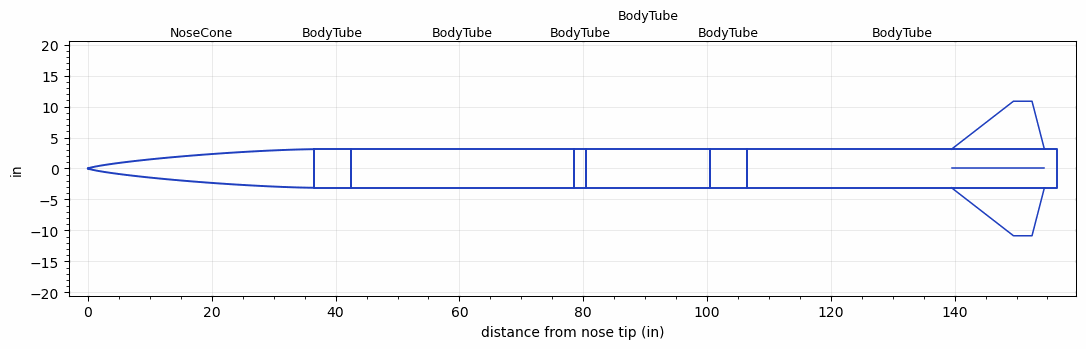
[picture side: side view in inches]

<RASAeroDocument>
 <FileVersion>2</FileVersion>
 <RocketDesign>
  <NoseCone>
   <Length>36.5</Length>
   <Diameter>6.23</Diameter>
   <Shape>Von Karman Ogive</Shape>
   <BluntRadius>0.05</BluntRadius>
   <Location>0</Location>
  </NoseCone>
  <BodyTube>
   <Length>6</Length>
   <Diameter>6.23</Diameter>
   <Location>36.5</Location>
  </BodyTube>
  <BodyTube>
   <Length>36</Length>
   <Diameter>6.23</Diameter>
   <Location>42.5</Location>
  </BodyTube>
  <BodyTube>
   <Length>2</Length>
   <Diameter>6.23</Diameter>
   <Location>78.5</Location>
   <Protuberance>
    <StreamlinedNoBaseDrag>0</StreamlinedNoBaseDrag>
    <StreamlinedWithBaseDrag>0.122</StreamlinedWithBaseDrag>
    <InclinedPlate1Angle>0</InclinedPlate1Angle>
    <InclinedPlate1FrontalArea>0</InclinedPlate1FrontalArea>
    <InclinedPlate2Angle>0</InclinedPlate2Angle>
    <InclinedPlate2FrontalArea>0</InclinedPlate2FrontalArea>
   </Protuberance>
  </BodyTube>
  <BodyTube>
   <Length>20</Length>
   <Diameter>6.23</Diameter>
   <Location>80.5</Location>
  </BodyTube>
  <BodyTube>
   <Length>6</Length>
   <Diameter>6.23</Diameter>
   <Location>100.5</Location>
   <Protuberance>
    <StreamlinedNoBaseDrag>1.87</StreamlinedNoBaseDrag>
    <StreamlinedWithBaseDrag>0</StreamlinedWithBaseDrag>
    <InclinedPlate1Angle>0</InclinedPlate1Angle>
    <InclinedPlate1FrontalArea>0</InclinedPlate1FrontalArea>
    <InclinedPlate2Angle>0</InclinedPlate2Angle>
    <InclinedPlate2FrontalArea>0</InclinedPlate2FrontalArea>
   </Protuberance>
  </BodyTube>
  <BodyTube>
   <Length>50</Length>
   <Diameter>6.23</Diameter>
   <LaunchShoeArea>0.183</LaunchShoeArea>
   <Location>106.5</Location>
   <Fin>
    <Count>4</Count>
    <Chord>15</Chord>
    <Span>7.75</Span>
    <SweepDistance>10</SweepDistance>
    <TipChord>3</TipChord>
    <Thickness>0.255</Thickness>
    <LERadius>0.0313</LERadius>
    <Location>17</Location>
    <AirfoilSection>Hexagonal</AirfoilSection>
    <FX1>0.35</FX1>
    <FX3>0.35</FX3>
   </Fin>
  </BodyTube>
  <Surface>Smooth Paint</Surface>
  <ModifiedBarrowman>True</ModifiedBarrowman>
  <Turbulence>True</Turbulence>
  <UseBooster1>False</UseBooster1>
  <UseBooster2>False</UseBooster2>
 </RocketDesign>
 <LaunchSite>
  <Altitude>2930</Altitude>
  <Pressure>0</Pressure>
  <RodAngle>5</RodAngle>
  <RodLength>17</RodLength>
  <Temperature>85</Temperature>
  <WindSpeed>0</WindSpeed>
 </LaunchSite>
 <Recovery>
  <Altitude1>1000</Altitude1>
  <Altitude2>1400</Altitude2>
  <DeviceType1>Parachute</DeviceType1>
  <DeviceType2>Parachute</DeviceType2>
  <Event1>True</Event1>
  <Event2>True</Event2>
  <Size1>36</Size1>
  <Size2>120</Size2>
  <EventType1>Apogee</EventType1>
  <EventType2>Altitude</EventType2>
  <CD1>1.33</CD1>
  <CD2>2</CD2>
 </Recovery>
 <SimulationList>
  <Simulation>
   <SustainerEngine>O4350-WY623-I26a-T  (WVUER2026)</SustainerEngine>
   <SustainerLaunchWt>125</SustainerLaunchWt>
   <SustainerNozzleDiameter>2.89</SustainerNozzleDiameter>
   <SustainerCG>111</SustainerCG>
   <SustainerIgnitionDelay>0</SustainerIgnitionDelay>
   <Booster1SeparationDelay>0</Booster1SeparationDelay>
   <Booster1IgnitionDelay>0</Booster1IgnitionDelay>
   <IncludeBooster1>False</IncludeBooster1>
   <Booster2Delay>0</Booster2Delay>
   <IncludeBooster2>False</IncludeBooster2>
   <TimetoApogee>43.88864</TimetoApogee>
   <MaxAltitude>33884.68</MaxAltitude>
   <MaxVelocity>1789.563</MaxVelocity>
  </Simulation>
 </SimulationList>
</RASAeroDocument>
